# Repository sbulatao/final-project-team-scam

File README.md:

# SolutionForpollution
GitHub Repo for ECE 196 Project Managing code, PCB files, 3D design, and more.

## WEBSITES: 
https://scam.196.aiya.lol/

https://final-project-team-scam.onrender.com

## Structure:
- css file contains all the css: the style for the website

- pictures file contains all the pictures: jpeg, png, etc.

- public file contains all the js: the action-ish for the website

- views file contains all the html: the bone structure for the website

## PROBLEM DEFINTION
Stormwater and Sewage Spills contain untreated debris directly into the Tijuana River and Imperial Beach affecting pH of the waters affecting marine life and making it more acidic.

## PROPOSED IDEA
A Real-Time Water pH Regulation Network

 - Big idea is pumping in basic solution in untreated water to regulate pH for marine life
 - Starting with pH sensor to determine levels, and pumping basic solution until it’s a regular level

## TESTABLE HYPOTHESIS
If there is polluted water with a more acidic pH, then our device will read the values and add basic solution until the pH is regular/safe for marine life.

## MILESTONES / TIMELINE
1. Completed PCB design on KiCAD and received parts from shipping
2. Assembled PCB with all necessary SMD’s and components and verified successful communication with computer (the device is recognized)
3. Finished 3D printing for basic solution enclosure, path for tube, body for contaminated water and measurement, and plastic cup to gather and pour water (not 3D printed)
4. Completed code for pH sensor data collection and logging to read and display pH values over time for both regular and contaminated water, with pH data collected and tabulated
5. Finished code and hardware integration for pumping with connections to PCB and recognizing pump in Arduino, basic solution can travel in pump to water and stop pumping when correct pH is read. 
6. Testing and data collection in Untreated Water, testing out conditions for demo by recording video of shown, unclean dirty water with higher pH levels and showing pumping solution regulating pH levels until level is sustainable for marine life.

## References, Citations, Helpful Resources

# HTML References
FreeFrontend. 2016-2024. https://freefrontend.com/css-water-effects/

HTML5UP. https://html5up.net/ (Didn't Use but thinking about it)

## Research / Arduino Build

Fahad, Engr. Electronic Clinic. 8 March 2020. IOT Water Quality Monitoring Using Arduino, pH Sensor, Nodemcu ESP8266. https://www.electroniclinic.com/iot-water-quality-monitoring-using-arduinoph-sensornodemcu-esp8266/

Ani, Emmanuel. hackster.io. 4 May 2024. Water Quality Monitoring and Notification System. https://www.hackster.io/eani/water-quality-monitoring-and-notification-system-f85d23 

YSI: a company that works on the water quality measurement which is The Sydney Institute of Marine Science collaborative
https://www.ysi.com/

United States Environmental Protection Agency. 21 October 2024. Water Quality Standards: Regulations and Resources. https://www.epa.gov/wqs-tech

Standard Methods For the Examination of Water and Wastewater. https://www.standardmethods.org

https://www.nsf.org/nsf-standards/standards-portfolio/water-wastewater-standards

(ERROR 404 GIVEN) https://www.nsf.org/our-services/water-quality

(ERROR 404 GIVEN) https://www.instructables.com/howto/water+quality+monitor/

## Website for the San Diego Coast Keepers EVIDENCE:

- Home page. https://www.sdcoastkeeper.org/
- Stormwater Infrastructure. https://www.sdcoastkeeper.org/water-quality/stormwater-infrastructure-funding/
- Tijuana River Sewage Crisis. https://www.sdcoastkeeper.org/tijuana-river-sewage/

## Other EVIDENCE:

Museg, Phillip. San Diego CoastKeeper. 2 May 2024. Understanding The Tijuana River Sewage Crisis - An Overview of Causes and Consequences. https://www.sdcoastkeeper.org/blog/tijuana-river-sewage-crisis-causes-consequences/

The California Water Boards. 25 September 2024. USIBWC Spill Events and Transboundary Flow Events from Mexico into the San Diego Region. https://www.waterboards.ca.gov/sandiego/water_issues/programs/tijuana_river_valley_strategy/sewage_issue.html

SDSU News Team. 14 February 2024. New Report: Public Health Crisis Unfolds as Tijuana River Sewage Contamination Escalates. https://www.sdsu.edu/news/2024/02/public-health-crisis-unfolds-as-tijuana-river-sewage-contamination-escalates

Shin, Tony. Fox 5 Kusi News. 11 September 2024. Imperial Beach Sewage Crisis Causing Fears of Long-Term Illnesses. https://fox5sandiego.com/news/local-news/imperial-beach-sewage-crisis-causing-fears-of-long-term-illnesses/#:~:text=The%20odor%20comes%20from%20millions,closed%20for%20over%201%2C000%20days.

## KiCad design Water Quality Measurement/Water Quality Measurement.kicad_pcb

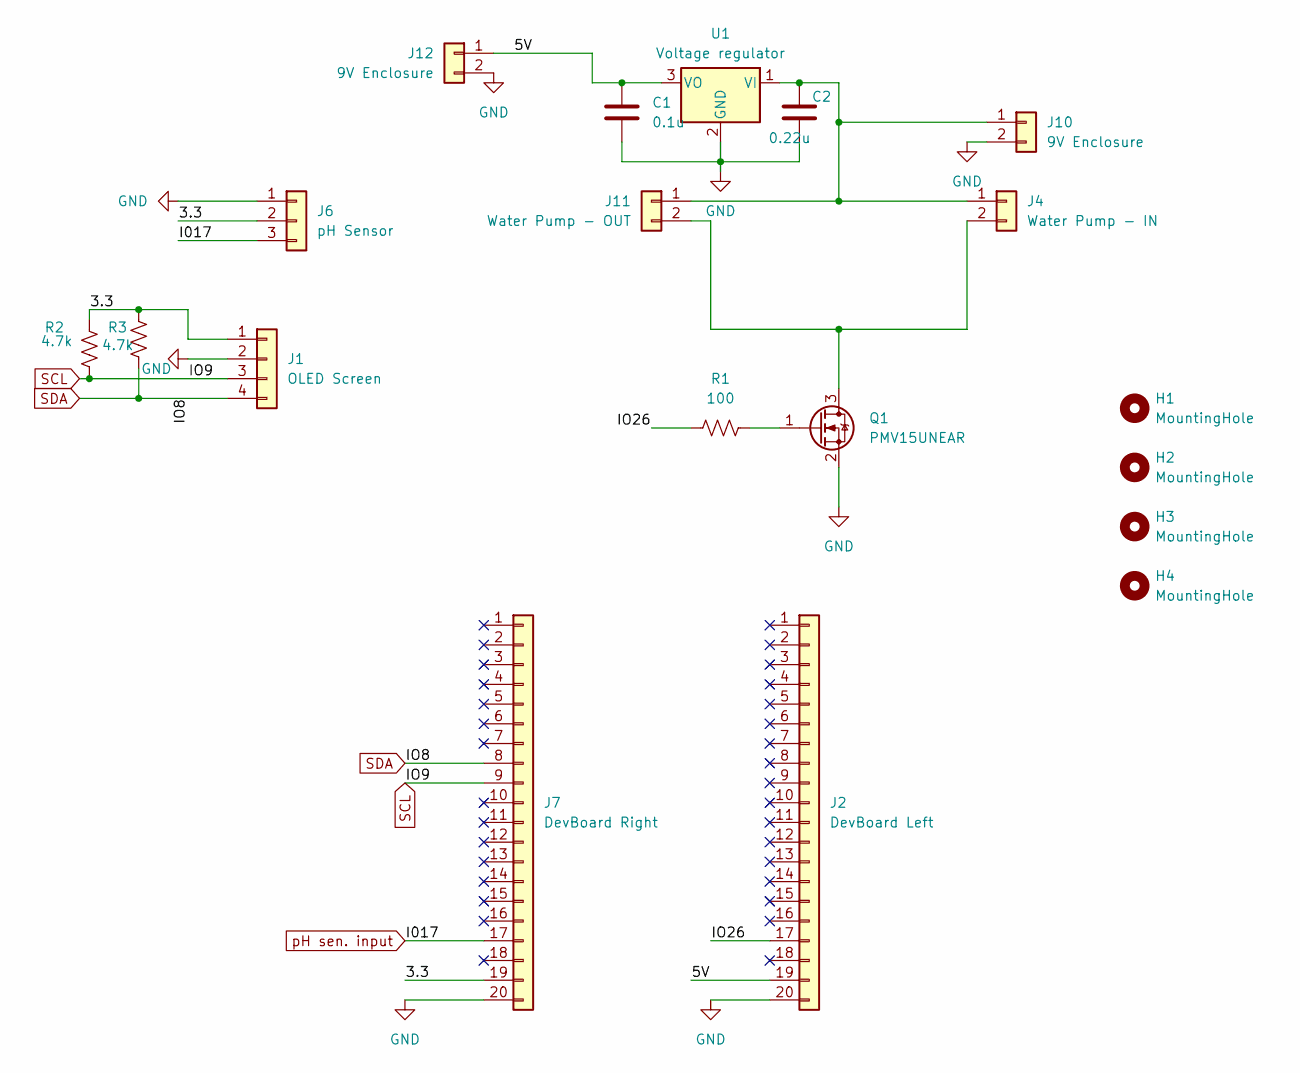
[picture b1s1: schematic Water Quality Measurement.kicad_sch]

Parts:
C1: 0.1u; C_0805_2012Metric_Pad1.18x1.45mm_HandSolder
C2: 0.22u; C_0805_2012Metric_Pad1.18x1.45mm_HandSolder
H1, H2, H3, H4: MountingHole; MountingHole_3.2mm_M3_ISO7380_Pad_TopBottom
J1: OLED Screen; PinHeader_1x04_P2.54mm_Vertical
J2: DevBoard Left; PinHeader_1x20_P2.54mm_Vertical
J4: Water Pump - IN; PinHeader_1x02_P2.54mm_Vertical
J6: pH Sensor; PinHeader_1x03_P2.54mm_Vertical
J7: DevBoard Right; PinHeader_1x20_P2.54mm_Vertical
J10, J12: 9V Enclosure; PinHeader_1x02_P2.54mm_Vertical
J11: Water Pump - OUT; PinHeader_1x02_P2.54mm_Vertical
Q1: PMV15UNEAR; SOT-23
R1: 100; R_1206_3216Metric
R2, R3: 4.7k; R_2010_5025Metric
U1: Voltage regulator; TO-220-3_Vertical

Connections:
/3.3: J1.1, J6.2, J7.19, R2.2, R3.2
/5V: C1.1, J2.19, J12.1, U1.3 (VO)
/IO26: J2.17, R1.1
GND: C1.2, C2.2, J1.2, J2.20, J6.1, J7.20, J10.2, J12.2, Q1.2 (S), U1.2 (GND)
unnamed: C2.1, J4.1, J10.1, J11.1, U1.1 (VI)
unnamed: J4.2, J11.2, Q1.3 (D)
unnamed: Q1.1 (G), R1.2
SCL: J1.3, J7.9, R2.1
SDA: J1.4, J7.8, R3.1
pH sen. input: J6.3, J7.17

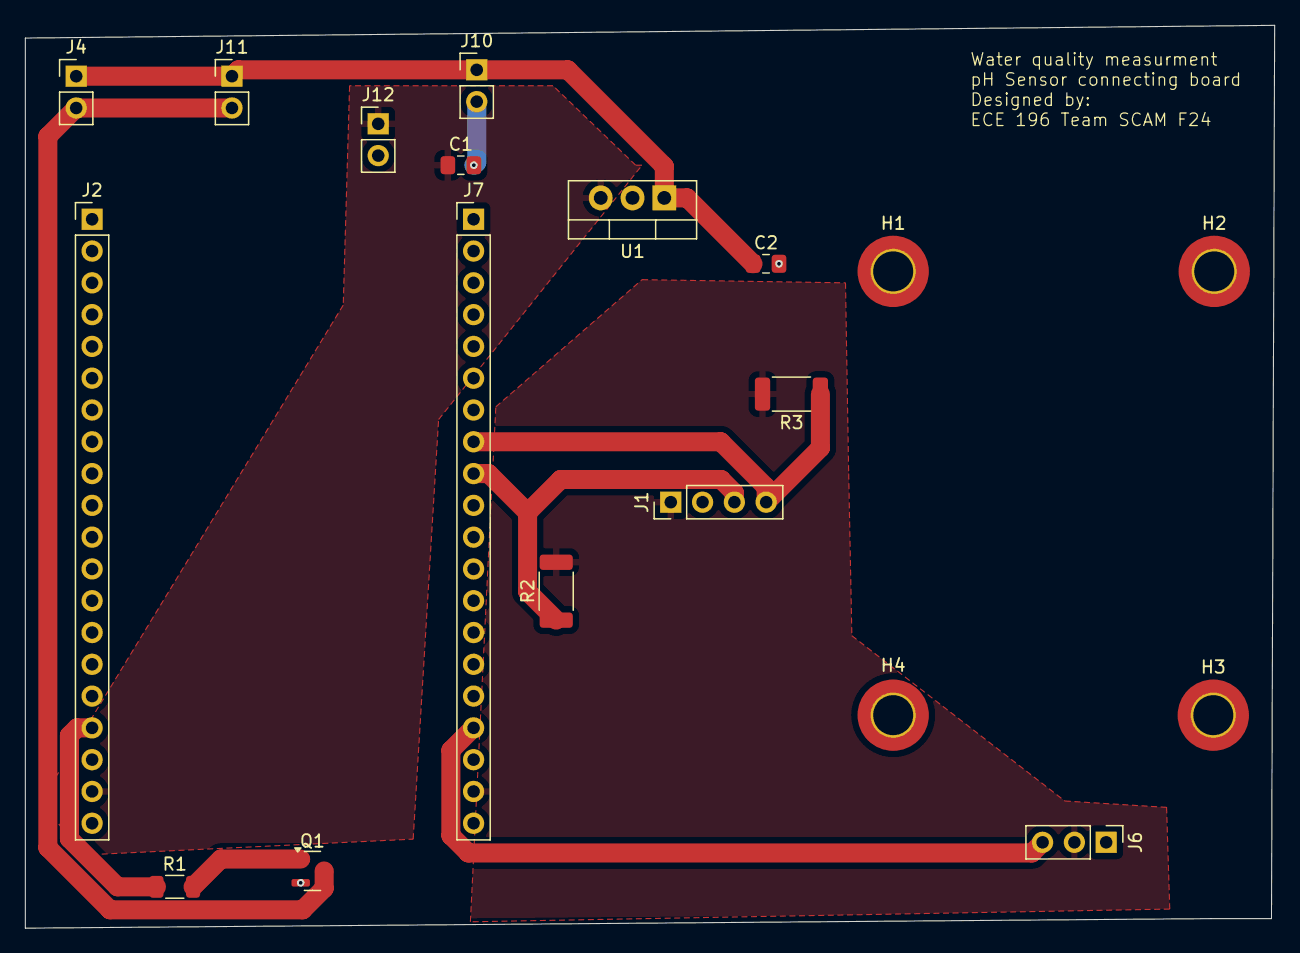
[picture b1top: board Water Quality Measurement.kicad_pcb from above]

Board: 2 copper layers, 99.8 x 72.1 mm, 19 parts (0 on the bottom side), 10 nets.

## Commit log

2024-10-29 Repo Copy
    Copied items from private repo to official one
2024-10-29 Removed unnecessary files
2024-10-29 added style to css, added menu bar to miniProject & resources
2024-10-29 Added water theme
2024-10-30 better layout i guess
2024-10-30 fixing aesthetics on lower body logo
2024-10-30 added milestones on milestones and timelines
2024-10-30 added info in team section for sarah
2024-10-30 updating README.md with info from slides
2024-10-30 moved schematic/pcb circuit/3D view to pictures file
2024-10-31 added schematic pictures in schematic section
2024-10-31 fixed schematic layout
2024-11-04 fixing layout
2024-11-05 added src
2024-11-05 uhhh
2024-11-05 added website
2024-11-05 added requirements.txt
2024-11-05 fixed poster stuff
2024-11-05 added Afraz bio
2024-11-05 added video note and poster stuff
2024-11-05 added diagram
2024-11-05 added another website
2024-11-07 ADDED more references in README.md
2024-11-14 added OLED codes for testing
2024-11-14 added ironman pic
2024-11-14 added OLED snowflake pic
2024-11-14 added layout code for water pump
2024-11-18 updating milestones and timeline info
2024-11-18 in progress: milstone&timeline
2024-11-18 menu-bar hover white
2024-11-19 added more info in milestone&timeline
2024-11-19 updated milestone as of now
2024-11-19 update homepage, milestone, etc.
2024-11-19 Fixing aesthetics :3
2024-11-19 fixing teammate aesthetics
2024-11-19 pic a lil bigger
2024-11-19 fixing aesthetics stuff :3
2024-11-19 added template link :3
2024-11-20 more updates added & getting ready for database being added
2024-11-23 added layout for pHSensor database and graphing it
2024-11-23 added .cpp for esp32 for pHSensor values - in progress
2024-11-23 need to install library, gave site
2024-12-02 added main.ino file for microcontroller
2024-12-02 updated milestone
2024-12-03 updated #4 on milestones
2024-12-03 this works
2024-12-03 added pump status & servo status
2024-12-03 updating main.cpp
2024-12-03 just updating
2024-12-03 updating poster section
2024-12-03 idk whats going on
2024-12-03 added firebase-admin in requirement.txt
2024-12-03 meep
2024-12-03 added matplotlib on requirement.txt for website
2024-12-04 aaaahhhh
2024-12-04 hopefully this works
2024-12-04 updated homepage
2024-12-04 pls work
2024-12-06 Merge
2024-12-06 Updatd teammates
    Added contributions of Afraz and Chloe to teammates page
2024-12-07 Added more text describing PCB and resources
2024-12-07 Updated PCB description again
2024-12-07 Lots of web changes
    Uupdated images, ECE department logo, favorites photos/content, added resource, etc.
2024-12-07 "Final Changes"
    Final changes
2024-12-07 Final committs for updating schematics with annotations
2024-12-07 Enclosure update
    Put in picture for enclosure
2024-12-07 added stuff in gitignore
2024-12-07 some updates
2024-12-07 layout stuff
2024-12-07 added teammate meep
2024-12-07 added github repo
2024-12-07 fixing stuff
2024-12-07 fix some aesthetics
2024-12-09 added chloes struggles
2024-12-18 adding video link
